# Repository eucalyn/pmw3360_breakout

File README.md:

# pmw3360_breakout
 pmw3360 Breackout PCB

## BOM list

| Name | Designator | Qty. |
| --- | --- | --- |
| PMW3360 | U1 | 1 |
| TCR2EF19,LM(CT | U2 | 1 |
| SN74LVC1T45QDCKRQ1 | U3 | 1 |
| TXB0104RUTR | U4 | 1 |
| 4.7uF 0603 Capacitor | C1 | 1 |
| 0.1uF 0603 Capacitor | C2 | 1 |
| 1uF 0603 Capacitor | C3,C4 | 2 |
| Hirose P1.25mm 07P Horizontal Connector | J1 | 1 |
| 39R 0603 Resistor | R1 | 1 |
| 10k 0603 Resistor | R2,R3 | 2 |

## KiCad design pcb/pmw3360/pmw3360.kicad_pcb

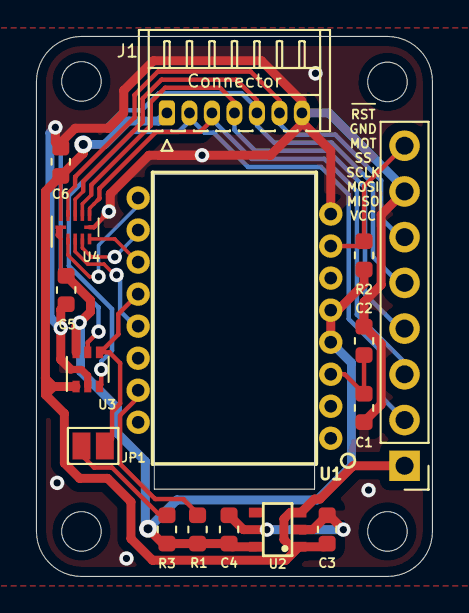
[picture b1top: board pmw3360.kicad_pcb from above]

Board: 2 copper layers, 22.0 x 30.0 mm, 16 parts (0 on the bottom side), 17 nets.

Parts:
C1: 4.7uF; C_0603_1608Metric
C2, C5, C6: 0.1uF; C_0603_1608Metric
C3, C4: 1uF; C_0603_1608Metric
J1: Connector; Hirose_DF13-07P-1.25DS_1x07_P1.25mm_Horizontal
J2: PinOut; PinHeader_1x08_P2.54mm_Vertical
JP1: JP_Open; SolderJumper-2_P1.3mm_Open_Pad1.0x1.5mm
R1: 39R; R_0603_1608Metric
R2, R3: 10k; R_0603_1608Metric
U1: PMW3360DM-T2QU; PMW3360
U2: TCR2EF19,LM(CT; SOT25
U3: SN74LVC1T45QDCKRQ1; SOT-363_SC-70-6
U4: TXB0104RUT; Texas_R_PUQFN-N12

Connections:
/MISO: JP1.1, U1.12, U3.4
/MISO-H: J1.2, J2.2, U3.3
/MOSI: U1.11, U4.5
/MOSI-H: J1.3, J2.3, U4.7
/MOT: U1.9, U4.2
/MOT-H: J1.6, J2.6, U4.10
/NRESET: J2.8, R2.2, U1.7
/SCLK: U1.10, U4.4
/SCLK-H: J1.4, J2.4, U4.8
/SS: U1.13, U4.3
/SS-H: J1.5, J2.5, U3.5, U4.9
GND: C1.2, C2.2, C3.2, C4.2, C5.1, C6.2, J1.7, J2.7, U1.8, U2.2, U3.2, U4.6
unnamed: C1.1, C2.1, U1.3
unnamed: JP1.2, R3.2
unnamed: R1.1, U1.15
VCC: C3.1, C6.1, J1.1, J2.1, U2.1, U2.3, U3.1, U4.11
VDD: C4.1, C5.2, R1.2, R2.1, R3.1, U1.4, U1.5, U2.5, U3.6, U4.1, U4.12

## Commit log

2021-07-13 add kicad files
    add initial files
2021-07-13 add BOM list
    add BOM list
2021-07-13 change track width
    change track width 0.25mm -> 0.2mm around TXB0104
2021-07-13 change C,R footprint
    Change C,R footprint 0805 -> 0603
    Change U3 position
2021-07-13 change silk position
    change silk position
2021-07-13 change parts position
2021-07-13 add PinOut silk
2021-07-13 add vias
2021-07-13 change route
2021-07-13 save .sch
2021-07-14 change footprints position
2021-07-14 Change U3 position
2021-07-14 routing
2021-07-14 change fab comment position
2021-07-14 add via
2021-07-14 add ignore files
    cache or bak files are ignored
2021-07-14 change route
    avoid mounting hole
2021-07-14 Change VCC, VDD track width
    Change VCC, VDD track width
    0.25mm -> 0.5mm
2021-07-20 change silk
2021-07-20 drill and place offset
2021-07-20 add gerber files
